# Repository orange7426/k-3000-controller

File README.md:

# k-3000-controller
Smart controller for K-3000 hand blender.

## Features

- **Non-instrusive**: The controller is a non-intrusive device. It controls the blender with original power inputs.
- **Control over internet**: Both WiFi and Bluetooth are supported. The project provides a default wifi interface. By proper proxy setting, it can be controlled from anywhere in the world.
- **Count each stroke**: The device "knows" the stroke being executed by measuing the motor current. It empowers user to add any arbitrary delay between strokes.

## Images

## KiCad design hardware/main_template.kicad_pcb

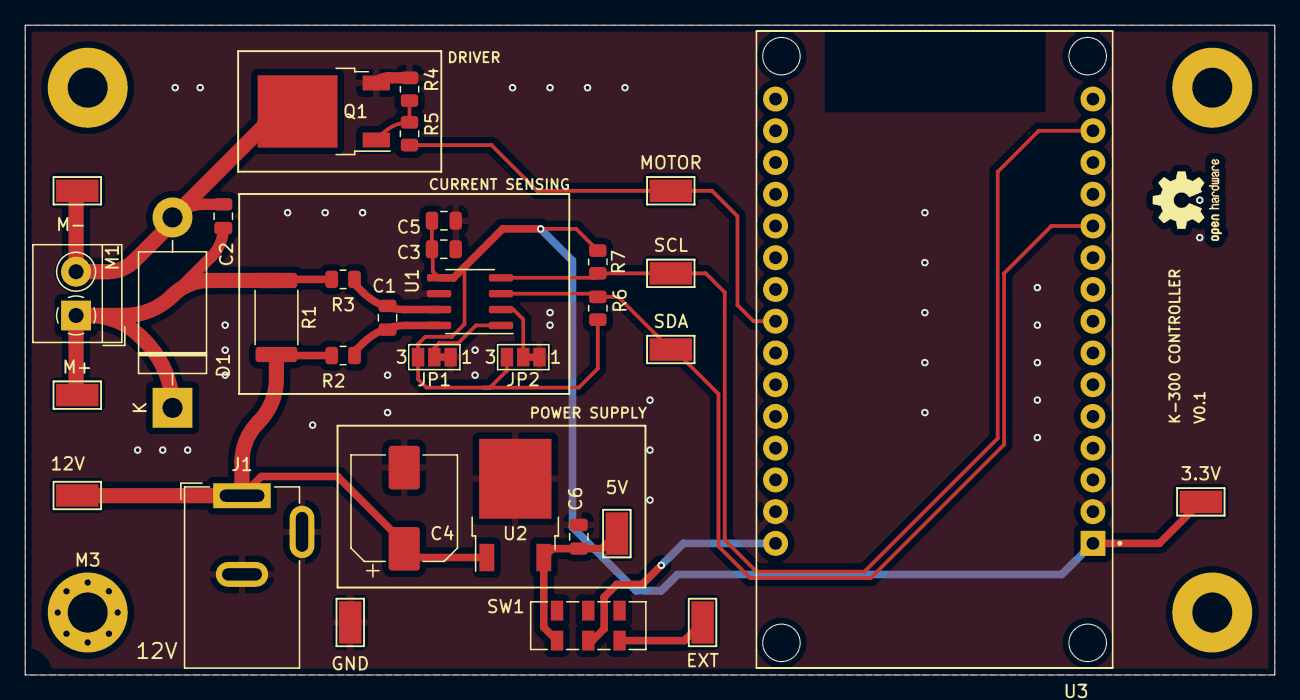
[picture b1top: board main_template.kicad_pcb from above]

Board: 4 copper layers, 100.0 x 52.0 mm, 34 parts (0 on the bottom side), 16 nets.

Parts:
3.3V, 5V, 12V: TestPoint; TestPoint_Keystone_5015_Micro-Minature
C1: DNP; C_0805_2012Metric
C2, C3: 1uF; C_0805_2012Metric
C4: 100uF; CP_Elec_8x10
C5, C6: 0.1uF; C_0805_2012Metric
D1: 1N5401; D_DO-201AD_P15.24mm_Horizontal
EXT: TestPoint; TestPoint_Keystone_5015_Micro-Minature
GND: TestPoint; TestPoint_Keystone_5015_Micro-Minature
J1: Barrel_Jack_Switch; BarrelJack_GCT_DCJ200-10-A_Horizontal
JP1, JP2: SolderJumper_3_Bridged12; SolderJumper-3_P1.3mm_Bridged12_Pad1.0x1.5mm_NumberLabels
M1: Motor_DC; TerminalBlock_4Ucon_1x02_P3.50mm_Horizontal
M3: MountingHole_3.2mm_M3_Pad_Via
M+: TestPoint; TestPoint_Keystone_5015_Micro-Minature
M-: TestPoint; TestPoint_Keystone_5015_Micro-Minature
MOTOR: TestPoint; TestPoint_Keystone_5015_Micro-Minature
Q1: STD7NK40Z; TO-252-2
R1: R100; R_2512_6332Metric
R2, R3, R5: 0; R_0805_2012Metric
R4: 10k; R_0805_2012Metric
R6, R7: 4.7K; R_0805_2012Metric
SCL: TestPoint; TestPoint_Keystone_5015_Micro-Minature
SDA: TestPoint; TestPoint_Keystone_5015_Micro-Minature
SW1: SW_DPDT_x2; SW_DPDT_CK_JS202011JCQN
U1: INA219AxD; SOIC-8_3.9x4.9mm_P1.27mm
U2: MC78M05_TO252; TO-252-2
U3: ESP32-DEVKIT-V1; MODULE_ESP32_DEVKIT_V1

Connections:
+3V3: 3.3V.1, C3.2, C5.2, JP1.3 (B), JP2.3 (B), R6.1, R7.1, U1.5 (VS), U3.1 (3V3)
+5V: 5V.1, C6.1, SW1.3 (C), U2.3 (VO)
+12V: 12V.1, C4.1, J1.1, R1.2, R2.2, U2.1 (VI)
/MOTOR: MOTOR.1, R5.1, U3.23 (D25)
/SCL: R7.2, SCL.1, U1.4 (SCL), U3.14 (D22)
/SDA: R6.2, SDA.1, U1.3 (SDA), U3.11 (D21)
GND: C3.1, C4.2, C5.1, C6.2, GND.1, J1.2, J1.3, JP1.1 (A), JP2.1 (A), Q1.3 (S), R4.2, U1.6 (GND), U2.2 (GND), U3.2 (GND), U3.29 (GND)
unnamed: C1.1, R3.1, U1.7 (IN-)
unnamed: C1.2, R2.1, U1.8 (IN+)
unnamed: C2.1, D1.1 (K), M1.1 (+), M+.1, R1.1, R3.2
unnamed: C2.2, D1.2 (A), M1.2 (-), M-.1, Q1.2 (D)
unnamed: JP1.2 (C), U1.1 (A1)
unnamed: JP2.2 (C), U1.2 (A0)
unnamed: Q1.1 (G), R4.1, R5.2
unnamed: EXT.1, SW1.1 (A)
unnamed: SW1.2 (B), U3.30 (VIN)

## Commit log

2022-07-01 Add hardware schematic and pcb layout
2022-07-01 Add software source code
2022-07-01 Add diagram and images
2022-07-01 Add readme
2022-07-01 upload gerber zip
